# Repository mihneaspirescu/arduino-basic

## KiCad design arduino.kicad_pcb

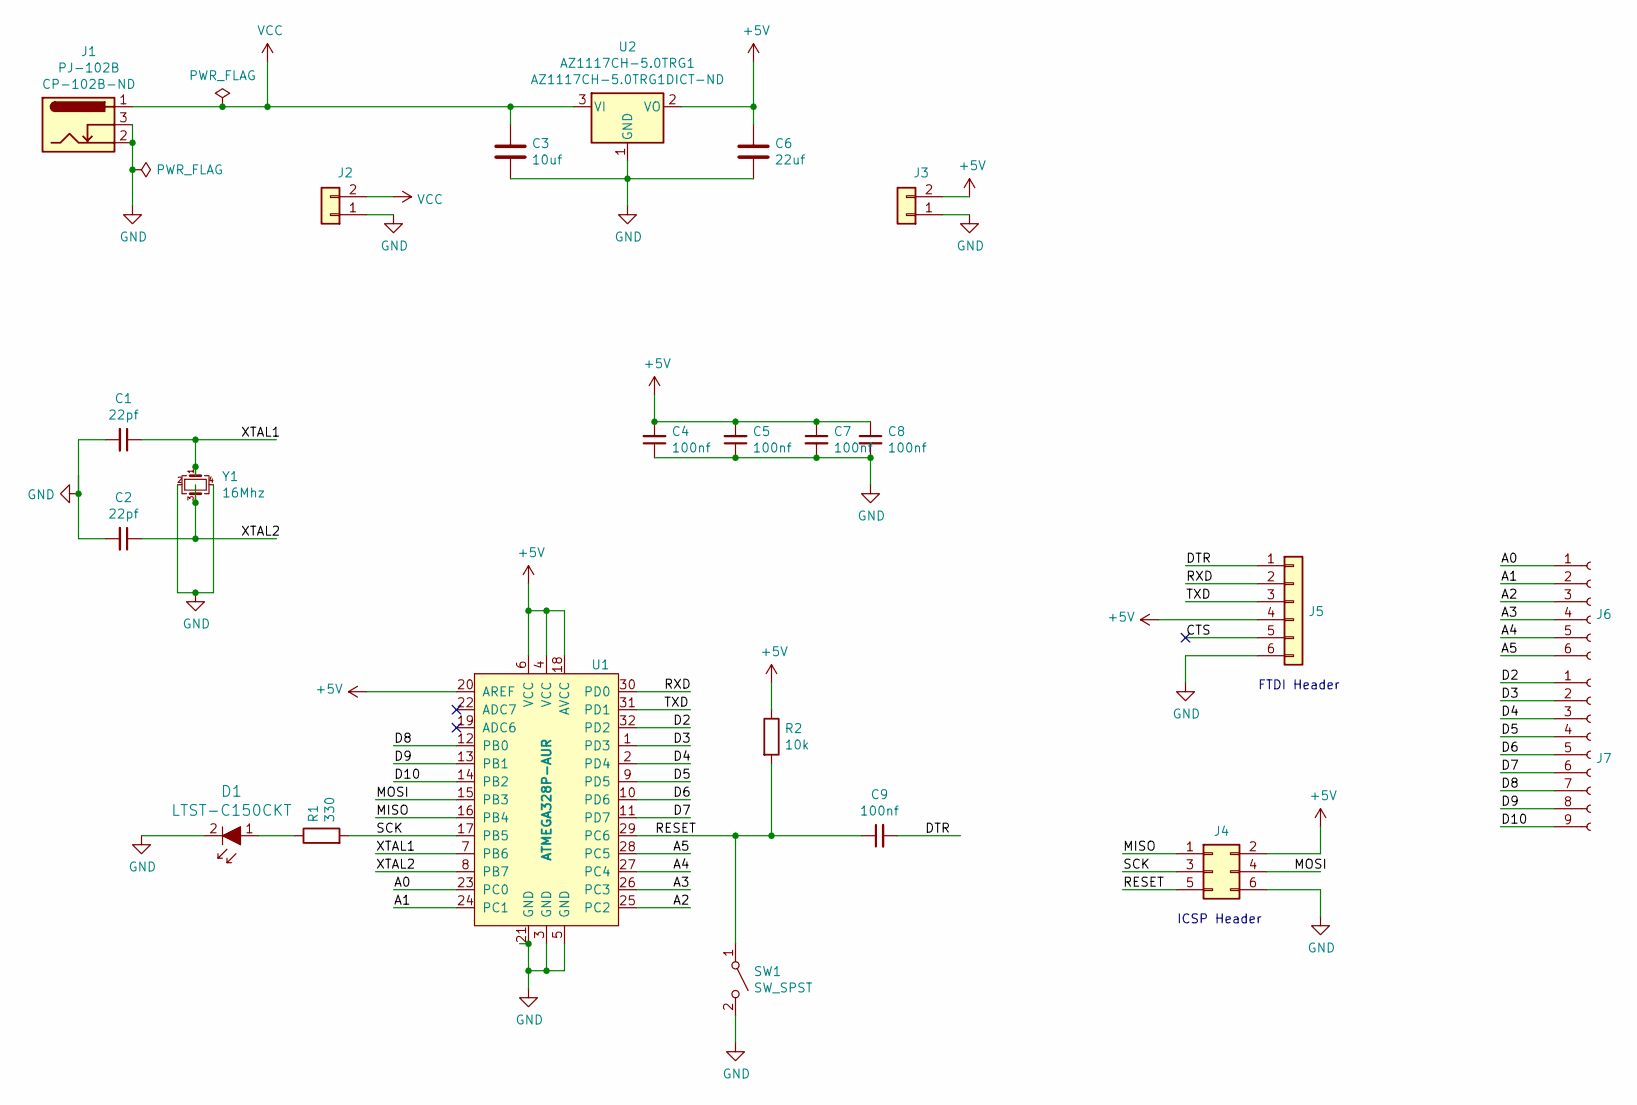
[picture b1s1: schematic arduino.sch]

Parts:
C1, C2: 22pf; C_0805_2012Metric_Pad1.15x1.40mm_HandSolder; Digikey 399-1113-1-ND
C3: 10uf; C_0805_2012Metric_Pad1.15x1.40mm_HandSolder; Digikey 490-5519-1-ND
C4, C5, C7, C8, C9: 100nf; C_0805_2012Metric_Pad1.15x1.40mm_HandSolder; Digikey 399-1177-1-ND
C6: 22uf; C_0805_2012Metric_Pad1.15x1.40mm_HandSolder; Digikey 490-10749-1-ND
D1: LTST-C150CKT; 1206; MPN LTST-C150CKT; Digikey 160-1167-1-ND
J1: PJ-102B; CUI_PJ-102B; Digikey CP-102B-ND
J2, J3: Conn_01x02; PinHeader_1x02_P2.54mm_Vertical
J4: Conn_02x03_Counter_Clockwise; PinHeader_2x03_P2.54mm_Vertical
J5: Conn_01x06; PinHeader_1x06_P2.54mm_Vertical
J6: Conn_01x06_Female; PinHeader_1x06_P2.54mm_Vertical
J7: Conn_01x09_Female; PinHeader_1x09_P2.54mm_Vertical
R1: 330; 0805; Digikey A129743CT-ND
R2: 10k; 0805; Digikey 311-10.0KCRCT-ND
SW1: SW_SPST; SW_SPST_TL3342; Digikey EG5470CT-ND
U1: ATMEGA328P-AUR; TQFP-32_7x7mm; MPN ATMEGA328P-AUR; Digikey ATMEGA328P-AURCT-ND
U2: AZ1117CH-5.0TRG1; SOT-223-3_TabPin2; Digikey AZ1117CH-5.0TRG1DICT-ND
Y1: 16Mhz; Crystal_SMD_3225-4Pin_3.2x2.5mm; Digikey SER4069CT-ND

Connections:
+5V: C4.2, C5.2, C6.1, C7.1, C8.1, J3.2, J4.2, J5.4, R2.1, U1.4 (VCC), U1.6 (VCC), U1.18 (AVCC), U1.20 (AREF), U2.2 (VO)
/A0: J6.1, U1.23 (PC0)
/A1: J6.2, U1.24 (PC1)
/A2: J6.3, U1.25 (PC2)
/A3: J6.4, U1.26 (PC3)
/A4: J6.5, U1.27 (PC4)
/A5: J6.6, U1.28 (PC5)
/CTS: J5.5
/D2: J7.1, U1.32 (PD2)
/D3: J7.2, U1.1 (PD3)
/D4: J7.3, U1.2 (PD4)
/D5: J7.4, U1.9 (PD5)
/D6: J7.5, U1.10 (PD6)
/D7: J7.6, U1.11 (PD7)
/D8: J7.7, U1.12 (PB0)
/D9: J7.8, U1.13 (PB1)
/D10: J7.9, U1.14 (PB2)
/DTR: C9.2, J5.1
/MISO: J4.1, U1.16 (PB4)
/MOSI: J4.4, U1.15 (PB3)
/RESET: C9.1, J4.5, R2.2, SW1.1 (A), U1.29 (PC6)
/RXD: J5.2, U1.30 (PD0)
/SCK: J4.3, R1.2, U1.17 (PB5)
/TXD: J5.3, U1.31 (PD1)
/XTAL1: C1.1, U1.7 (PB6), Y1.1
/XTAL2: C2.1, U1.8 (PB7), Y1.3
GND: C1.2, C2.2, C3.2, C4.1, C5.1, C6.2, C7.2, C8.2, D1.2, J1.2, J1.3, J2.1, J3.1, J4.6, J5.6, SW1.2 (B), U1.3 (GND), U1.5 (GND), U1.21 (GND), U2.1 (GND), Y1.2, Y1.4
unnamed: D1.1, R1.1
VCC: C3.1, J1.1, J2.2, U2.3 (VI)

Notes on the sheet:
ICSP Header
FTDI Header

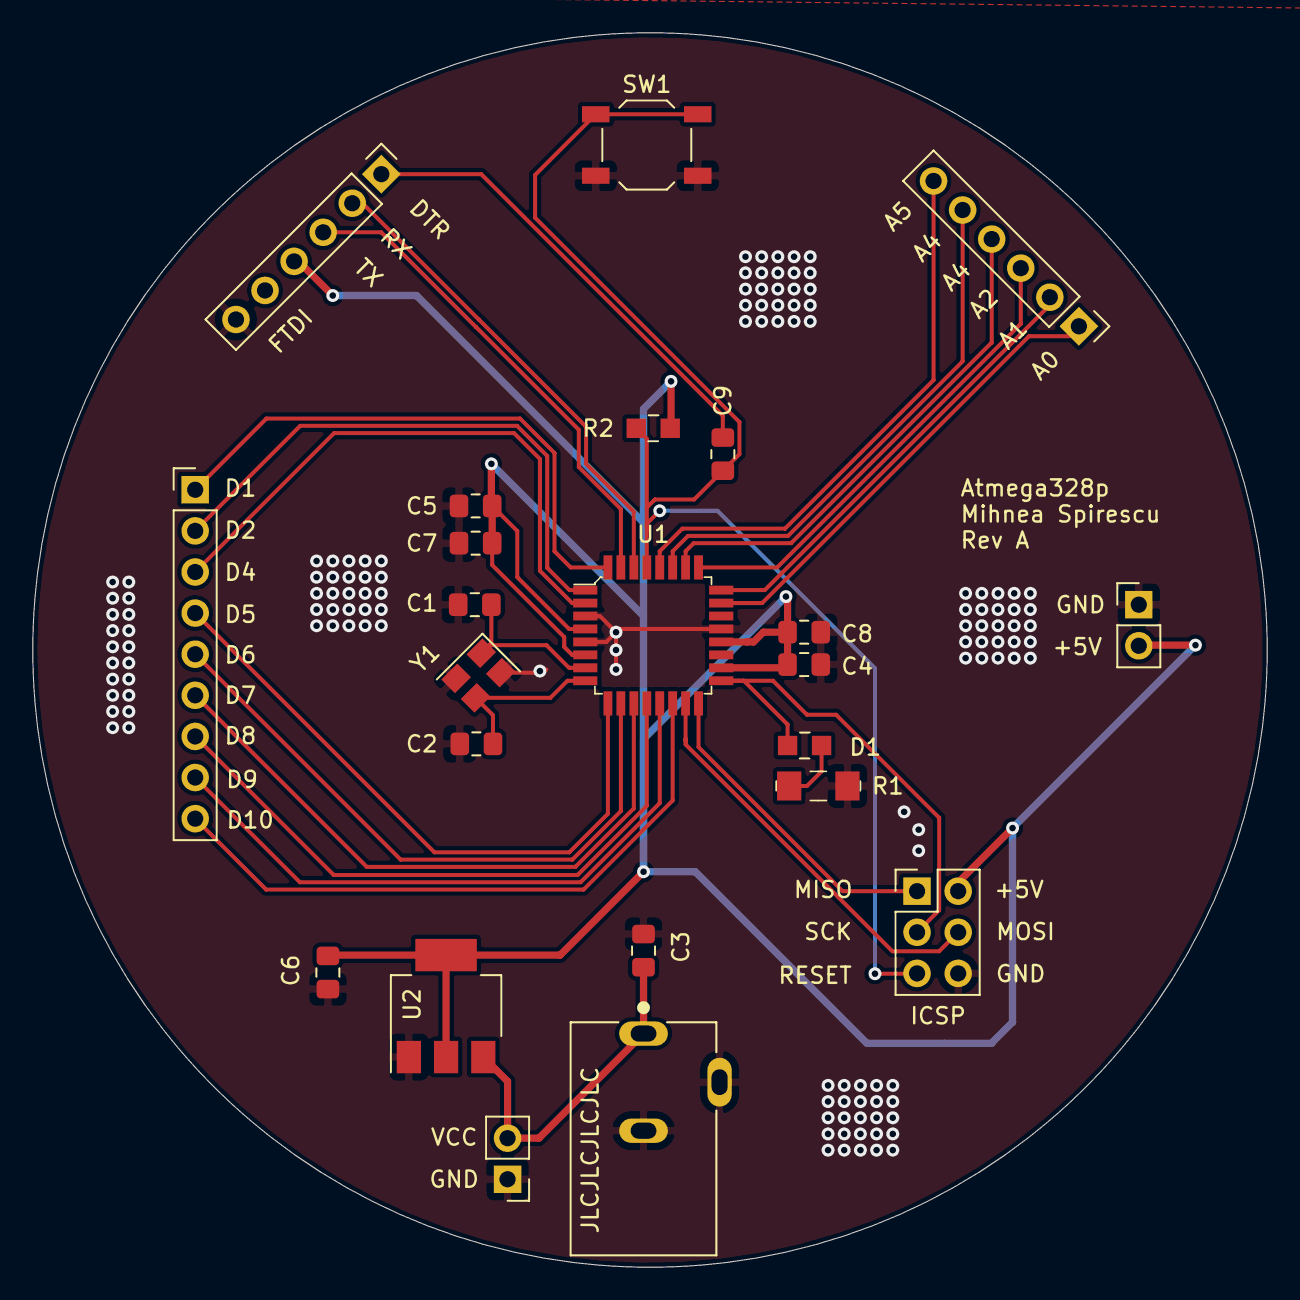
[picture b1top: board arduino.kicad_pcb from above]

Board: 2 copper layers, 76.3 x 76.3 mm, 23 parts (0 on the bottom side), 28 nets.

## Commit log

2020-08-16 v1 of arduino board
2020-08-16 added gitignore
2020-08-16 fix pushed files
2020-08-16 removed gerber
2020-08-16 added id from production
2020-08-16 removed unnecessary files
